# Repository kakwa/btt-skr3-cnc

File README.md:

# btt-skr3-cnc

Reviving a [Yeti Tool SmartBench](https://www.yetitool.com/) CNC router with new hardware and open-source firmware.

This project replaces pretty much all the sketchy eletronics original electronics with an even sketckier setup.

It keeps the original stepper motors, overal frame, and endstops.

## Project Status

* [done] Pi configuration
* [done] Base grblHAL setup
* [done] Wiring/adapter board
* [in-progress] End stops and safety stop configuration
* [in-progress] Proper enclosure for electronics
* [todo] Spindle control (optional)

## Hardware & Software components

| Component           | Details                                                          |
|---------------------|------------------------------------------------------------------|
| Controller board    | [BTT SKR 3 EZ](https://github.com/bigtreetech/SKR-3)             |
| Stepper drivers     | TMC5160                                                          |
| SBC                 | [BTT Pi](https://github.com/bigtreetech/BTT-Pi) (or RPi > 3)     |
| Firmware            | [grblHAL](https://github.com/grblHAL/core/blob/master/README.md) |
| UI & gCode Uploader | [gSender](https://sienci.com/gsender/)                           |
| Motors Setup        | X, Y, Z + ganged X2, Y2                                          |

## Repository Layout

- `docs/` — project documentation (start here); numbered markdown files covering intro, hardware, install, configuration, troubleshooting, and settings
- `ansible/` — Ansible playbook to provision the BTT Pi (roles: avahi, gsender, grblhal-builder, nginx, ...)
- `grblhal/` — grblHAL firmware as a git submodule (STM32 driver)
- `pcbs/` — KiCad PCB designs for the DB25 breakout boards and adapters
- `cad/` — FreeCAD enclosure and mounting parts
- `tests/` — G-code test files
- `misc/` — utility scripts and raw settings dumps

## Documentation

Project documentation is available in [`docs/`](docs/).

Salut c'est yann

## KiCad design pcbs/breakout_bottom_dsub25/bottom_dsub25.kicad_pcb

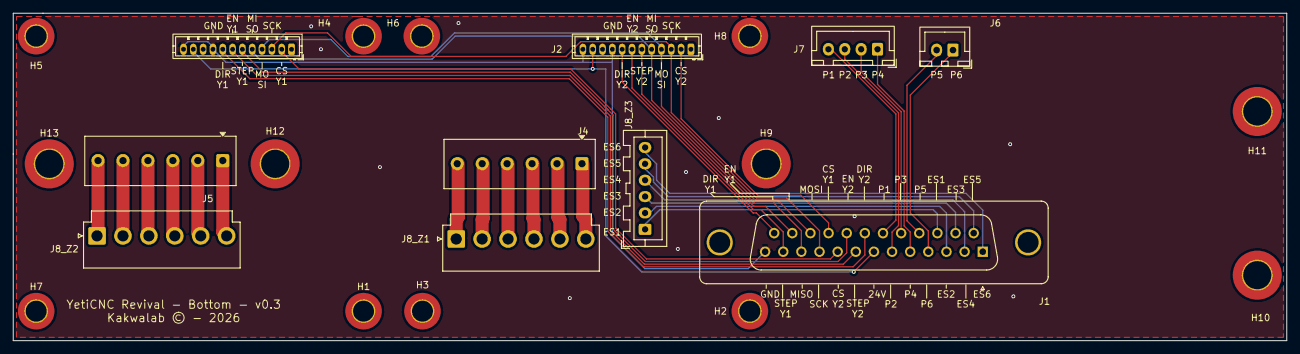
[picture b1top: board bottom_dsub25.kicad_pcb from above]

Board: 2 copper layers, 194.5 x 50.0 mm, 23 parts (0 on the bottom side), 37 nets.

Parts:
H1, H2, H3, H4, H5, H6, H7, H8: MountingHole; MountingHole_3.2mm_M3_DIN965_Pad_TopBottom
H9, H10, H11, H12, H13: MountingHole; MountingHole_4.3mm_M4_DIN965_Pad_TopBottom
J1: DB25_Pins; DSUB-25_Pins_Vertical_P2.77x2.84mm_MountingHoles
J2, J3: Conn_01x12; JST_ZH_B12B-ZR_1x12_P1.50mm_Vertical
J4, J5: Screw_Terminal_01x06; TerminalBlock_Phoenix_MKDS-1-6-3.81_1x06_P3.81mm_Horizontal
J6: Conn_01x02; JST_XH_B2B-XH-A_1x02_P2.50mm_Vertical
J7: Conn_01x04; JST_XH_B4B-XH-A_1x04_P2.50mm_Vertical
J8_Z1, J8_Z2: Conn_01x06_Pin; JST_VH_B6P-VH_1x06_P3.96mm_Vertical
J8_Z3: Conn_01x06_Pin; JST_XA_B06B-XASK-1_1x06_P2.50mm_Vertical

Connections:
GND: J1.13, J2.9, J2.12, J3.9, J3.12
unnamed: J1.14, J8_Z3.5
unnamed: J1.15, J8_Z3.3
unnamed: J1.16, J8_Z3.1
unnamed: J1.17, J6.2
unnamed: J1.18, J7.2
unnamed: J1.19, J7.4
unnamed: J1.20, J3.8
unnamed: J1.21, J3.6
unnamed: J1.22, J2.2
unnamed: J1.23, J2.4, J3.4
unnamed: J1.24, J2.6
unnamed: J1.25, J2.8
unnamed: J1.10, J2.3, J3.3
unnamed: J1.11, J2.5, J3.5
unnamed: J1.12, J2.7
unnamed: J1.7, J2.11, J3.11
unnamed: J1.9, J3.2
unnamed: J1.8, J3.7
unnamed: J4.1, J8_Z1.6
unnamed: J4.2, J8_Z1.5
unnamed: J4.3, J8_Z1.4
unnamed: J4.4, J8_Z1.3
unnamed: J4.5, J8_Z1.2
unnamed: J4.6, J8_Z1.1
unnamed: J5.1, J8_Z2.6
unnamed: J5.2, J8_Z2.5
unnamed: J5.3, J8_Z2.4
unnamed: J5.4, J8_Z2.3
unnamed: J5.5, J8_Z2.2
unnamed: J5.6, J8_Z2.1
unnamed: J1.4, J6.1
unnamed: J1.5, J7.1
unnamed: J1.6, J7.3
unnamed: J1.3, J8_Z3.2
unnamed: J1.2, J8_Z3.4
unnamed: J1.1, J8_Z3.6

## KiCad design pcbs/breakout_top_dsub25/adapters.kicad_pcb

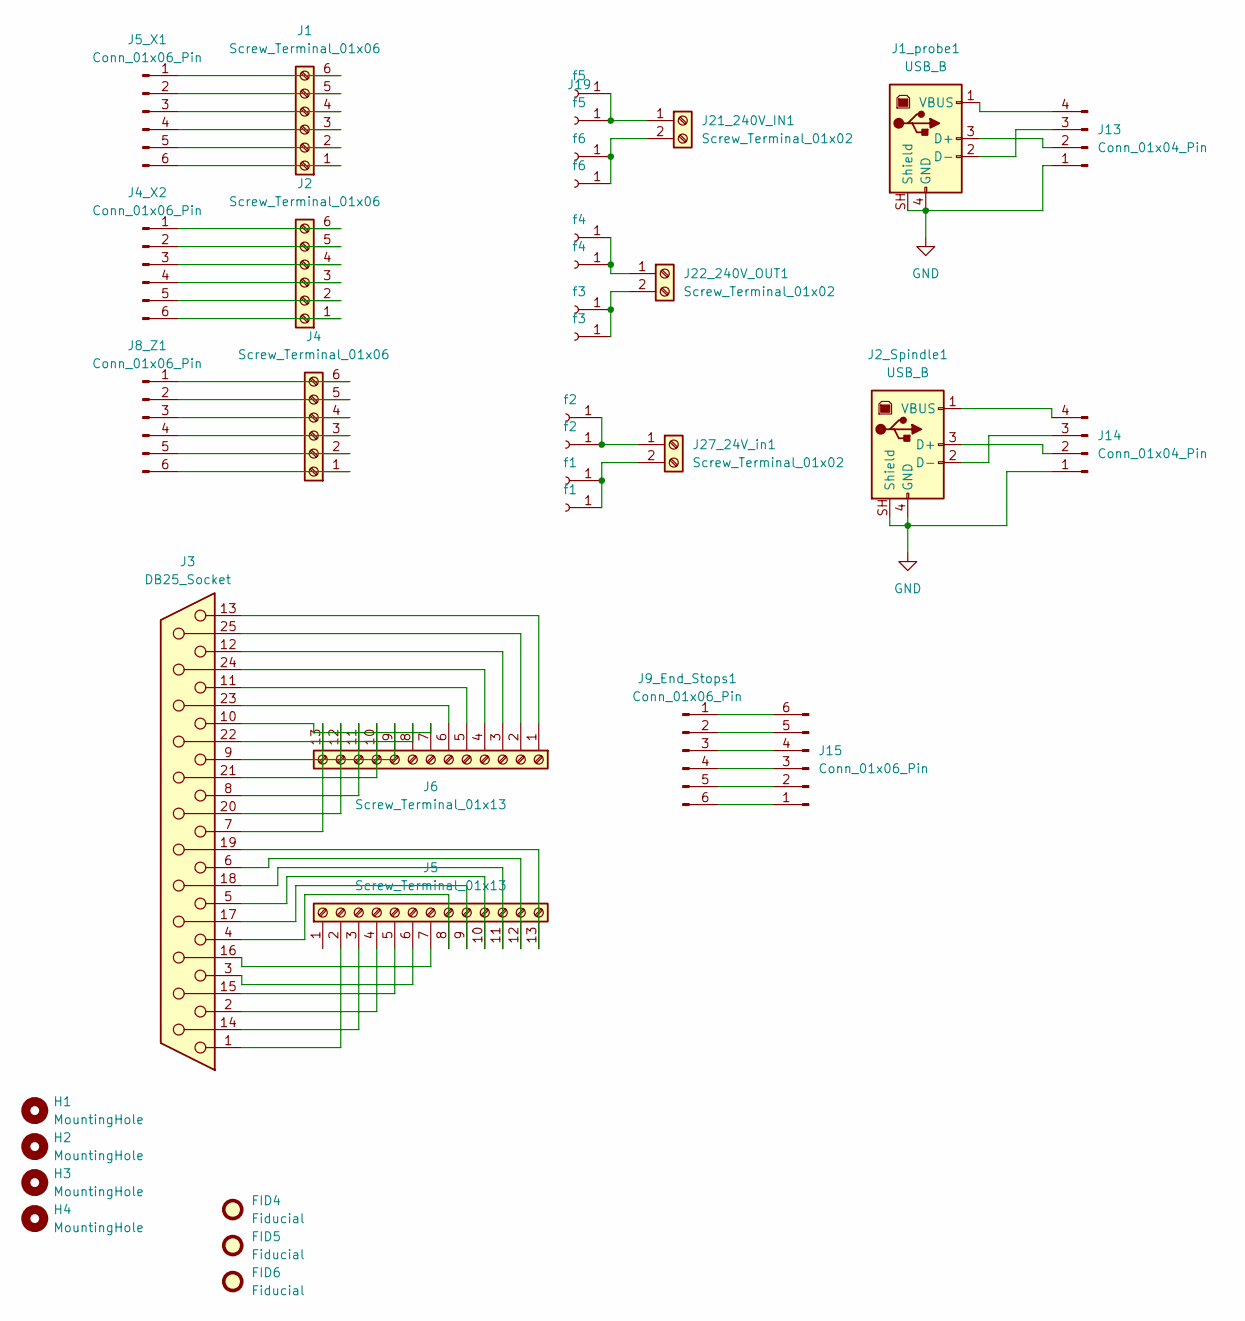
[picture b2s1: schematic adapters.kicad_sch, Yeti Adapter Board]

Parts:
F5: f5; SolderWire-1.5sqmm_1x01_D1.7mm_OD3mm
FID4, FID5, FID6: Fiducial; Fiducial_0.5mm_Mask2mm
H1, H2, H3, H4: MountingHole; MountingHole_3.2mm_M3_Pad_TopBottom
J1, J2, J4: Screw_Terminal_01x06; TerminalBlock_Phoenix_MKDS-1-6-3.81_1x06_P3.81mm_Horizontal
J1_probe1, J2_Spindle1: USB_B; USB_B_Lumberg_2411_02_Horizontal
J3: DB25_Socket; DSUB-25_Socket_Horizontal_P2.77x2.54mm_EdgePinOffset9.40mm
J4_X2, J5_X1: Conn_01x06_Pin; JST_VH_S6P-VH_1x06_P3.96mm_Horizontal
J5, J6: Screw_Terminal_01x13; TerminalBlock_Phoenix_MKDS-1-13-3.81_1x13_P3.81mm_Horizontal
J8_Z1, J9_End_Stops1: Conn_01x06_Pin; JST_XA_S06B-XASK-1N-BN_1x06_P2.50mm_Horizontal
J10, J11: f3; SolderWire-1.5sqmm_1x01_D1.7mm_OD3mm
J12, J16: f4; SolderWire-1.5sqmm_1x01_D1.7mm_OD3mm
J13, J14: Conn_01x04_Pin; JST_XH_B4B-XH-A_1x04_P2.50mm_Vertical
J15: Conn_01x06_Pin; JST_XH_B6B-XH-A_1x06_P2.50mm_Vertical
J17, J18: f6; SolderWire-1.5sqmm_1x01_D1.7mm_OD3mm
J19: f5; SolderWire-1.5sqmm_1x01_D1.7mm_OD3mm
J21_240V_IN1, J22_240V_OUT1, J27_24V_in1: Screw_Terminal_01x02; TerminalBlock_Phoenix_MKDS-1,5-2_1x02_P5.00mm_Horizontal
J23, J24: f2; SolderWire-1.5sqmm_1x01_D1.7mm_OD3mm
J25, J26: f1; SolderWire-1.5sqmm_1x01_D1.7mm_OD3mm

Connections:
GND: J1_probe1.4 (GND), J1_probe1.SH (Shield), J2_Spindle1.4 (GND), J2_Spindle1.SH (Shield), J13.1, J14.1
unnamed: F5.1 (Pin_1_1), J19.1 (Pin_1_1), J21_240V_IN1.1
unnamed: J1.1, J5_X1.6
unnamed: J1.2, J5_X1.5
unnamed: J1.3, J5_X1.4
unnamed: J1.4, J5_X1.3
unnamed: J1.5, J5_X1.2
unnamed: J1.6, J5_X1.1
unnamed: J2.1, J4_X2.6
unnamed: J2.2, J4_X2.5
unnamed: J2.3, J4_X2.4
unnamed: J2.4, J4_X2.3
unnamed: J2.5, J4_X2.2
unnamed: J2.6, J4_X2.1
unnamed: J3.14, J5.3
unnamed: J3.15, J5.5
unnamed: J3.16, J5.7
unnamed: J3.17, J5.9
unnamed: J3.18, J5.11
unnamed: J3.19, J5.13
unnamed: J3.20, J6.12
unnamed: J3.21, J6.10
unnamed: J3.22, J6.8
unnamed: J3.23, J6.6
unnamed: J3.24, J6.4
unnamed: J3.25, J6.2
unnamed: J4.1, J8_Z1.6
unnamed: J4.2, J8_Z1.5
unnamed: J4.3, J8_Z1.4
unnamed: J4.4, J8_Z1.3
unnamed: J4.5, J8_Z1.2
unnamed: J4.6, J8_Z1.1
unnamed: J3.1, J5.2
unnamed: J3.2, J5.4
unnamed: J3.3, J5.6
unnamed: J3.4, J5.8
unnamed: J3.5, J5.10
unnamed: J3.6, J5.12
unnamed: J3.13, J6.1
unnamed: J3.12, J6.3
unnamed: J3.11, J6.5
unnamed: J3.10, J6.7
unnamed: J3.9, J6.9
unnamed: J3.8, J6.11
unnamed: J3.7, J6.13
unnamed: J10.1 (Pin_1_1), J11.1 (Pin_1_1), J22_240V_OUT1.2
unnamed: J12.1 (Pin_1_1), J16.1 (Pin_1_1), J22_240V_OUT1.1
unnamed: J1_probe1.3 (D+), J13.2
unnamed: J1_probe1.2 (D-), J13.3
unnamed: J1_probe1.1 (VBUS), J13.4
unnamed: J2_Spindle1.3 (D+), J14.2
unnamed: J2_Spindle1.2 (D-), J14.3
unnamed: J2_Spindle1.1 (VBUS), J14.4
unnamed: J9_End_Stops1.6, J15.1
unnamed: J9_End_Stops1.5, J15.2
unnamed: J9_End_Stops1.4, J15.3
unnamed: J9_End_Stops1.3, J15.4
unnamed: J9_End_Stops1.2, J15.5
unnamed: J9_End_Stops1.1, J15.6
unnamed: J17.1 (Pin_1_1), J18.1 (Pin_1_1), J21_240V_IN1.2
unnamed: J23.1 (Pin_1_1), J24.1 (Pin_1_1), J27_24V_in1.1
unnamed: J25.1 (Pin_1_1), J26.1 (Pin_1_1), J27_24V_in1.2

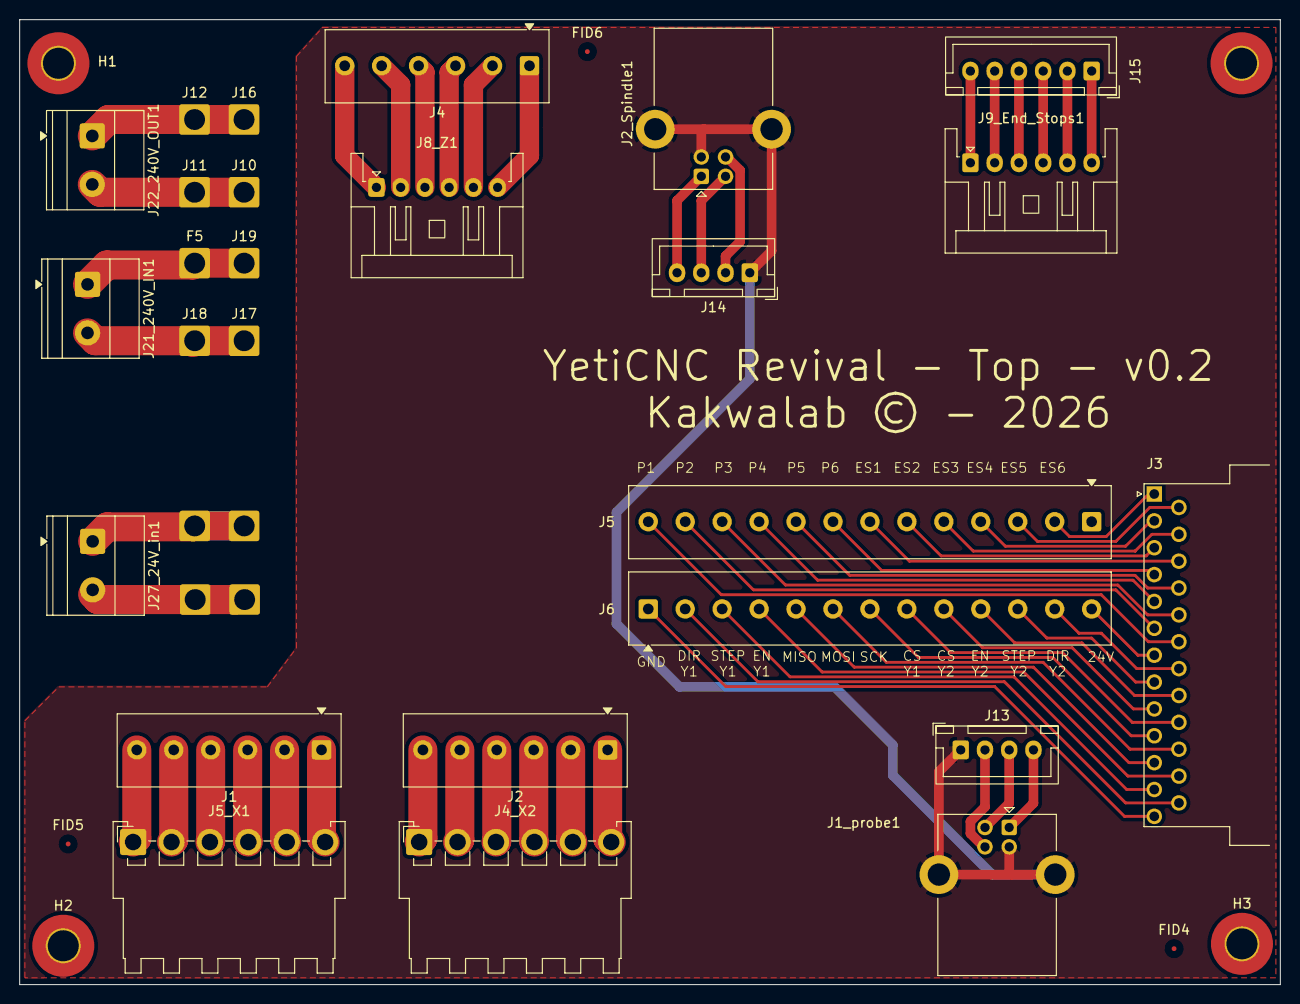
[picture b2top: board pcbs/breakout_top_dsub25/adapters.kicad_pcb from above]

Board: 2 copper layers, 130.0 x 99.5 mm, 37 parts (0 on the bottom side), 62 nets.

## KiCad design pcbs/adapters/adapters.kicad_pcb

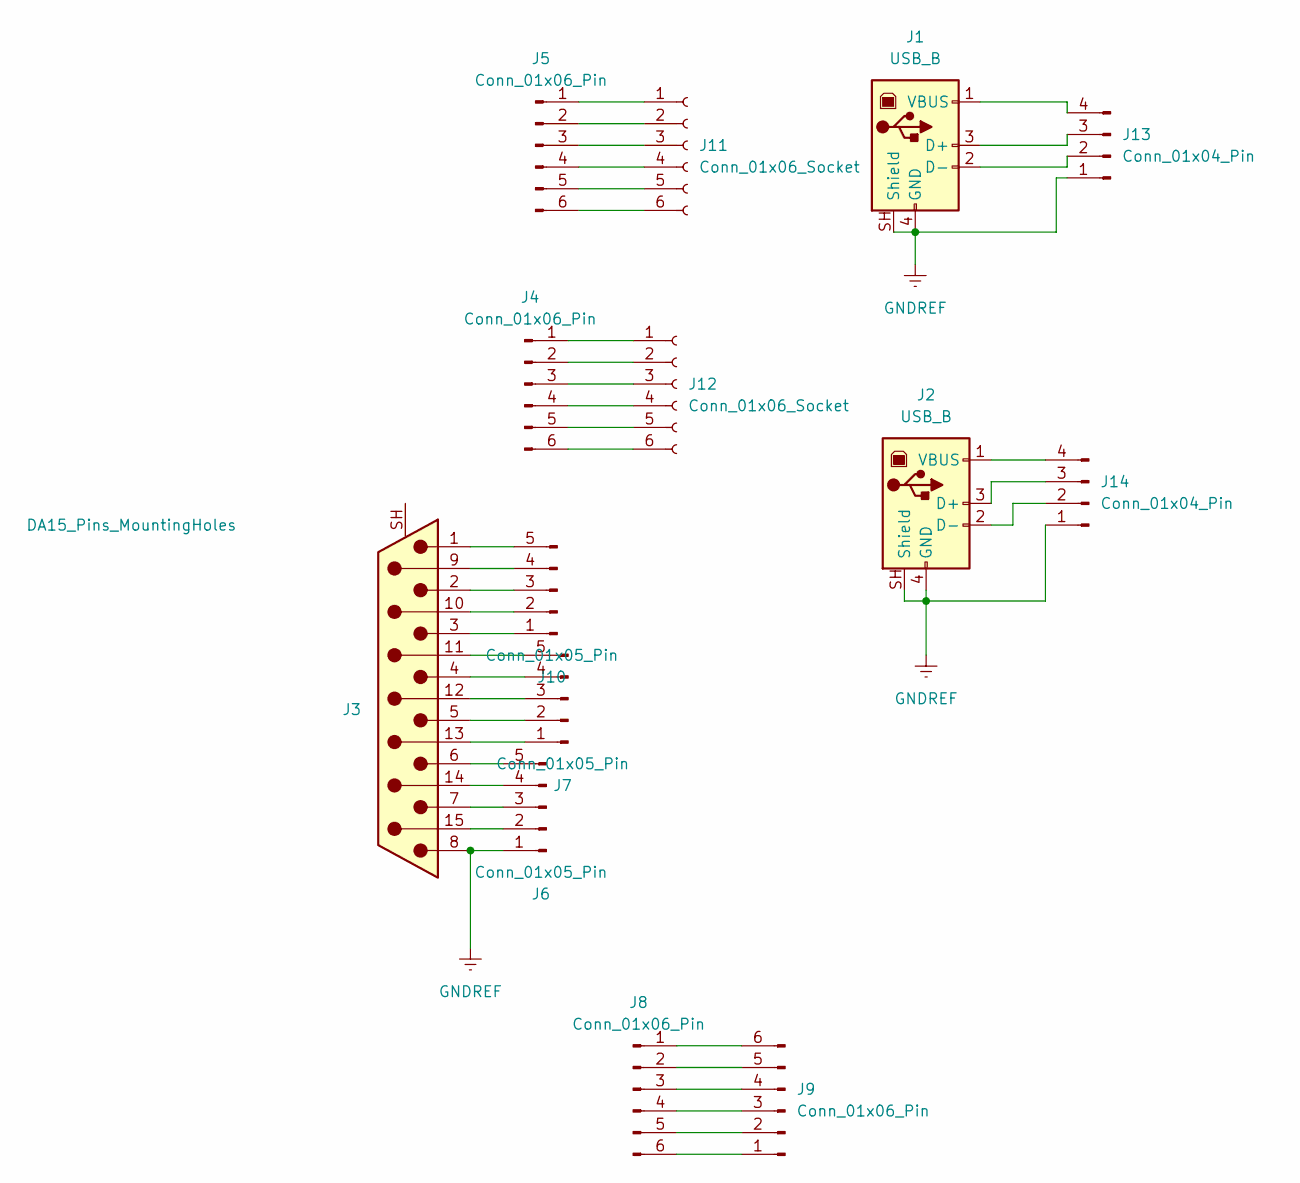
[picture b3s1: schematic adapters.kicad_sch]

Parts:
J1, J2: USB_B; USB_B_Lumberg_2411_02_Horizontal
J3: DA15_Pins_MountingHoles; DSUB-15-HD_Pins_Horizontal_P2.29x1.90mm_EdgePinOffset3.03mm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
J4, J5: Conn_01x06_Pin; JST_VH_S6P-VH_1x06_P3.96mm_Horizontal
J6, J7, J10: Conn_01x05_Pin; PinHeader_1x05_P2.54mm_Vertical
J8: Conn_01x06_Pin; JST_XA_S06B-XASK-1_1x06_P2.50mm_Horizontal
J9: Conn_01x06_Pin; PinHeader_1x06_P2.54mm_Vertical
J11, J12: Conn_01x06_Socket; PhoenixContact_MSTBA_2,5_6-G-5,08_1x06_P5.08mm_Horizontal
J13: Conn_01x04_Pin; PinHeader_1x04_P2.54mm_Vertical
J14: Conn_01x04_Pin

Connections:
GNDREF: J1.4 (GND), J1.SH (Shield), J2.4 (GND), J2.SH (Shield), J3.8, J6.1, J13.1, J14.1
unnamed: J1.3 (D+), J13.3
unnamed: J1.2 (D-), J13.2
unnamed: J1.1 (VBUS), J13.4
unnamed: J3.12, J7.3
unnamed: J3.13, J7.1
unnamed: J3.14, J6.4
unnamed: J3.15, J6.2
unnamed: J3.11 (P111), J7.5
unnamed: J3.7, J6.3
unnamed: J3.6, J6.5
unnamed: J3.5, J7.2
unnamed: J3.4, J7.4
unnamed: J8.1, J9.6
unnamed: J8.2, J9.5
unnamed: J8.3, J9.4
unnamed: J8.4, J9.3
unnamed: J8.5, J9.2
unnamed: J8.6, J9.1
unnamed: J3.3, J10.1
unnamed: J3.10, J10.2
unnamed: J3.2, J10.3
unnamed: J3.9, J10.4
unnamed: J3.1, J10.5
unnamed: J5.1, J11.1
unnamed: J5.2, J11.2
unnamed: J5.3, J11.3
unnamed: J5.4, J11.4
unnamed: J5.5, J11.5
unnamed: J5.6, J11.6
unnamed: J4.1, J12.1
unnamed: J4.2, J12.2
unnamed: J4.3, J12.3
unnamed: J4.4, J12.4
unnamed: J4.5, J12.5
unnamed: J4.6, J12.6
unnamed: J2.2 (D-), J14.2
unnamed: J2.3 (D+), J14.3
unnamed: J2.1 (VBUS), J14.4

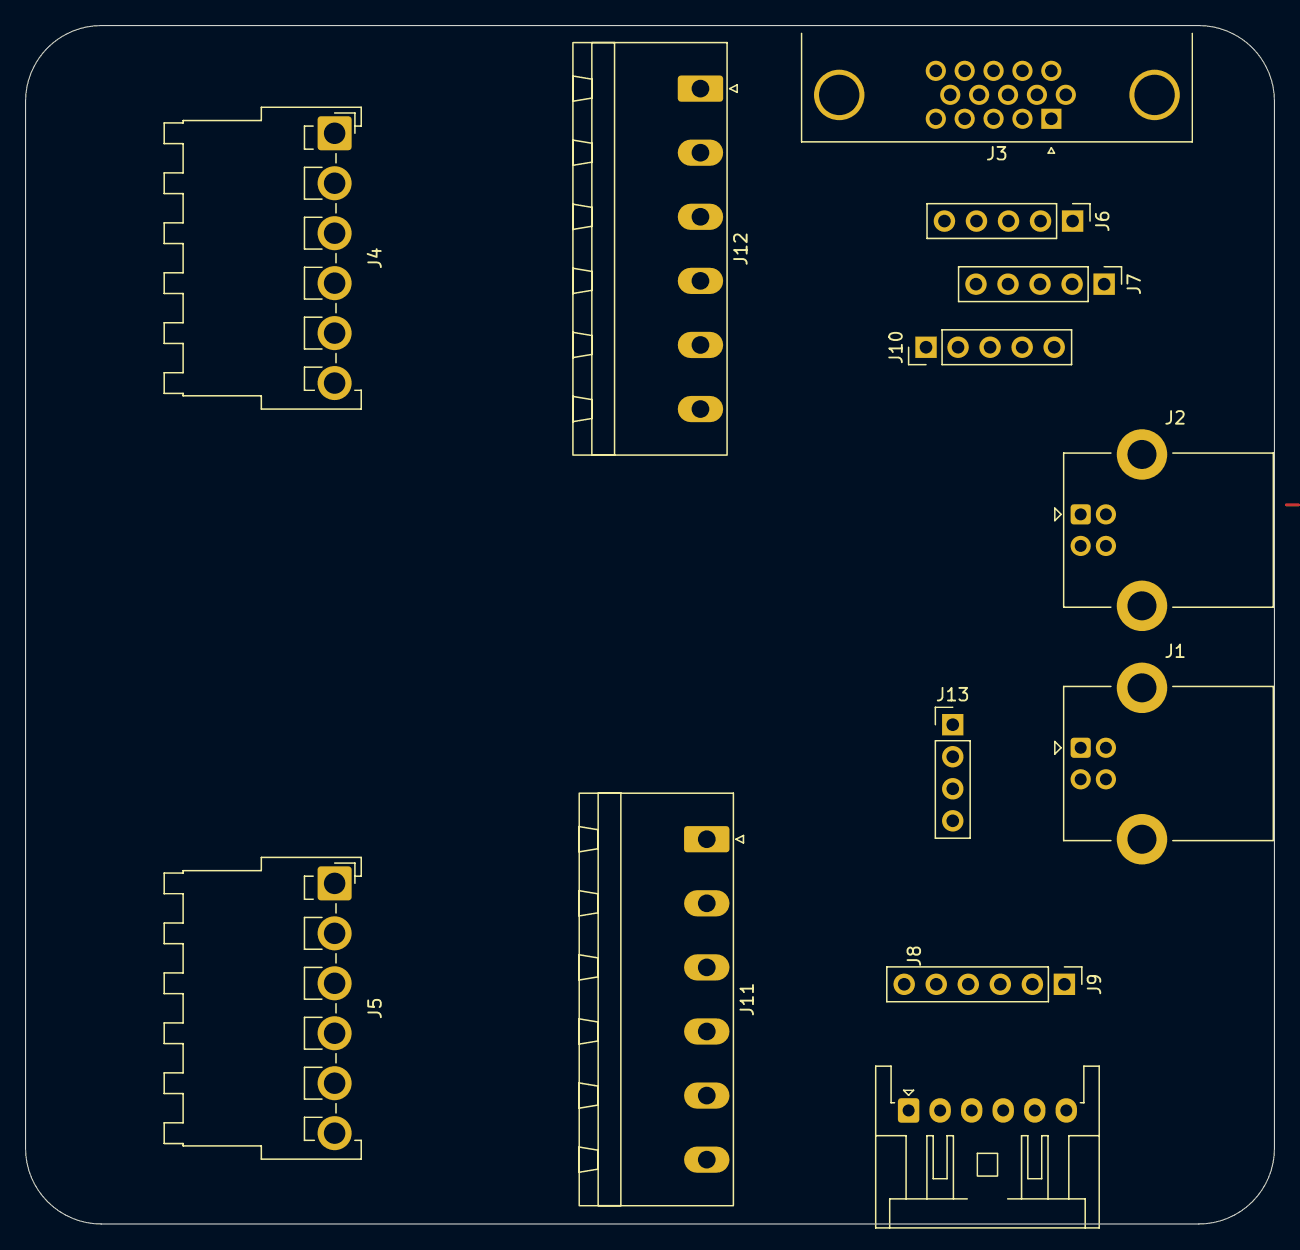
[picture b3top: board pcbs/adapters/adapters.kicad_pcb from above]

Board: 2 copper layers, 99.0 x 95.0 mm, 13 parts (0 on the bottom side), 36 nets.

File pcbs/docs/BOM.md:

# Bill of Materials

Every part: refdes, MPN, value, package, and WHY it was chosen. MPNs the agent
introduces without a datasheet check are flagged UNVERIFIED.

Value holds the component value only ("4.7uF", "1M", "500mAh Li-Po") — the
schematic stage draws it as the symbol's Value field, so a description there
collides with neighbouring symbols and fails the legibility gate. Prose belongs
in Rationale. One row per refdes; a grouped row ("C5-C8") matches no symbol.

| Refdes | Value | Footprint | MPN | Rationale |
|---|---|---|---|---|
| FID1 | Fiducial |  | UNVERIFIED | extracted from schematic by copperhead init |
| FID2 | Fiducial |  | UNVERIFIED | extracted from schematic by copperhead init |
| FID3 | Fiducial |  | UNVERIFIED | extracted from schematic by copperhead init |
| H1 | MountingHole | MountingHole:MountingHole_3.2mm_M3_DIN965_Pad_TopBottom | UNVERIFIED | extracted from schematic by copperhead init |
| H2 | MountingHole | MountingHole:MountingHole_3.2mm_M3_DIN965_Pad_TopBottom | UNVERIFIED | extracted from schematic by copperhead init |
| H3 | MountingHole | MountingHole:MountingHole_3.2mm_M3_DIN965_Pad_TopBottom | UNVERIFIED | extracted from schematic by copperhead init |
| H4 | MountingHole | MountingHole:MountingHole_3.2mm_M3_DIN965_Pad_TopBottom | UNVERIFIED | extracted from schematic by copperhead init |
| H5 | MountingHole | MountingHole:MountingHole_3.2mm_M3_DIN965_Pad_TopBottom | UNVERIFIED | extracted from schematic by copperhead init |
| H6 | MountingHole | MountingHole:MountingHole_3.2mm_M3_DIN965_Pad_TopBottom | UNVERIFIED | extracted from schematic by copperhead init |
| H7 | MountingHole | MountingHole:MountingHole_3.2mm_M3_DIN965_Pad_TopBottom | UNVERIFIED | extracted from schematic by copperhead init |
| H8 | MountingHole | MountingHole:MountingHole_3.2mm_M3_DIN965_Pad_TopBottom | UNVERIFIED | extracted from schematic by copperhead init |
| H9 | MountingHole | MountingHole:MountingHole_4.3mm_M4_DIN965_Pad_TopBottom | UNVERIFIED | extracted from schematic by copperhead init |
| H10 | MountingHole | MountingHole:MountingHole_4.3mm_M4_DIN965_Pad_TopBottom | UNVERIFIED | extracted from schematic by copperhead init |
| H11 | MountingHole | MountingHole:MountingHole_4.3mm_M4_DIN965_Pad_TopBottom | UNVERIFIED | extracted from schematic by copperhead init |
| H12 | MountingHole | MountingHole:MountingHole_4.3mm_M4_DIN965_Pad_TopBottom | UNVERIFIED | extracted from schematic by copperhead init |
| H13 | MountingHole | MountingHole:MountingHole_4.3mm_M4_DIN965_Pad_TopBottom | UNVERIFIED | extracted from schematic by copperhead init |
| J1 | DB25_Pins | Connector_Dsub:DSUB-25_Pins_Vertical_P2.77x2.84mm_MountingHoles | UNVERIFIED | extracted from schematic by copperhead init |
| J2 | Conn_01x12 | Connector_JST:JST_ZH_B12B-ZR_1x12_P1.50mm_Vertical | UNVERIFIED | extracted from schematic by copperhead init |
| J3 | Conn_01x12 | Connector_JST:JST_ZH_B12B-ZR_1x12_P1.50mm_Vertical | UNVERIFIED | extracted from schematic by copperhead init |
| J4 | Screw_Terminal_01x06 | TerminalBlock_Phoenix:TerminalBlock_Phoenix_MKDS-1-6-3.81_1x06_P3.81mm_Horizontal | UNVERIFIED | extracted from schematic by copperhead init |
| J5 | Screw_Terminal_01x06 | TerminalBlock_Phoenix:TerminalBlock_Phoenix_MKDS-1-6-3.81_1x06_P3.81mm_Horizontal | UNVERIFIED | extracted from schematic by copperhead init |
| J6 | Conn_01x02 | Connector_JST:JST_XH_B2B-XH-A_1x02_P2.50mm_Vertical | UNVERIFIED | extracted from schematic by copperhead init |
| J7 | Conn_01x04 | Connector_JST:JST_XH_B4B-XH-A_1x04_P2.50mm_Vertical | UNVERIFIED | extracted from schematic by copperhead init |
| J8_Z1 | Conn_01x06_Pin | Connector_JST:JST_VH_B6P-VH_1x06_P3.96mm_Vertical | UNVERIFIED | extracted from schematic by copperhead init |
| J8_Z2 | Conn_01x06_Pin | Connector_JST:JST_VH_B6P-VH_1x06_P3.96mm_Vertical | UNVERIFIED | extracted from schematic by copperhead init |
| J8_Z3 | Conn_01x06_Pin | Connector_JST:JST_XA_B06B-XASK-1_1x06_P2.50mm_Vertical | UNVERIFIED | extracted from schematic by copperhead init |

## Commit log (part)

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2026-01-16 base setup for ansible
2026-01-16 submodule
2026-01-16 remove repo
2026-01-16 clean-up
2026-01-16 add submodule for real this time
2026-01-16 skeleton for the gsender module
2026-01-16 update ansible submodule
2026-01-16 adding missing handler
2026-01-16 adding gsender service
2026-01-17 fix binary path for gsender
2026-01-17 adding the remote/headless flag
2026-01-17 use xvfb (gsender requires an X11 server)
2026-01-17 use wayland xwfb-run instead + gsender in video group
    a bit more futur process, and less complaints about acceleration (might
    also be because of group video
2026-01-17 switch to xwayland-run
2026-01-17 rsyslog tweaks
2026-01-19 notes
2026-01-22 adding notes
2026-01-23 grblhal submodule for STM32H7
2026-01-23 split nginx and gsenser role
2026-01-23 adding role to setup build tools for grblhal
2026-01-23 fixed ports for avahi
2026-01-24 workaround for build
2026-01-24 header + notes
2026-01-28 update grblhal
2026-01-28 adding rough version of my_machince.h
2026-01-28 deploy our configuration header
2026-01-28 adding symlink for convinience
2026-01-28 tweak build and flash + NOTES
2026-01-28 more complete documentation
2026-01-31 put the ganged #defined in the platform.io file (otherwise they don't seem to be takken into accont)
2026-01-31 switch to everything defined in my_machine.h
2026-02-19 update submodule
2026-03-17 remove personal roles
2026-03-17 adding instruction for the setup
2026-03-17 add basic setup instruction
2026-03-17 Fix repos role: install python3-debian dependency
    Made-with: Cursor
2026-03-17 Fix nginx role: use ansible_facts instead of deprecated ansible_hostname
    Made-with: Cursor
2026-03-17 re-enable repo setup
2026-03-17 Fix grblhal-builder role: use ansible_facts instead of deprecated ansible_architecture
    Made-with: Cursor
2026-03-17 Fix grblhal-builder defaults: use ansible_facts instead of deprecated ansible_user_id
    Made-with: Cursor
2026-03-17 Fix grblhal-builder: set build user/group to root explicitly
    Made-with: Cursor
2026-03-17 Fix grblhal-builder: allow platformio.ini to be copied so it can be patched
    Made-with: Cursor
2026-03-18 adding xauth
2026-03-18 adding an ignore errors for platformio init
2026-03-18 set limits and build number
2026-03-18 trigger apt cache update when appropriate
2026-03-18 complete the ansible stuff
2026-03-18 adding flashing instruction
2026-03-18 skeleton for the wiring
2026-03-18 basic pinout configuration
2026-03-18 enable the Safety Door ping (to be used for the collision bars)
2026-03-20 Add board labels and remove MAX switchs limits
2026-03-20 clean-up README
2026-03-21 adding documentation for pins
2026-03-21 tweaks
2026-03-21 customize btt_skr_v3.0_map.h directly
2026-04-11 adding todo list
2026-04-14 adding skeleton for pcb
2026-04-16 remove adapter
2026-04-29 PCB draft tweaks + ignores
2026-04-30 first rough version of top board
2026-05-01 rename
2026-05-01 adding a dsub 25 variant + tweaks
2026-05-03 adding project for bottom page
2026-05-07 progress on the bottom board (most connectors, etc)
2026-05-09 rough component positioning for bottom pcb + add connectors
2026-05-09 add routinng
2026-05-10 adding various silk layer labels
2026-05-10 tweak top board
    add mounting holes in the middle (enable zip for cables?)
    reposition a few components
    fix some rules warnings
2026-05-10 adding ground plan
2026-05-10 add version/name
2026-05-10 adding Makefile to generate the gerbel files
2026-05-10 don't commit zip files (gerbel)
2026-05-26 adding trying to set some inversion mask
2026-05-26 version bump
2026-05-28 Add DHCP server setup instructions for ethernet connectivity
2026-05-29 quick router setup script
2026-05-29 better README
2026-05-29 adding SDCARD definition
2026-06-04 adding stands cad model
2026-06-04 increase size of standoff
2026-06-10 4mm diameter for the stand legs of the driver mounts
2026-06-10 adding backplate for bottom PCB
2026-06-10 adding refresh page for nginx
2026-06-10 configuration clean-up
2026-06-13 trying to clean-up build
2026-06-13 lower current
2026-06-13 rollback grbhal
2026-06-15 more conservative values
2026-06-15 add cnc console helper + set grbhal to latest version
2026-06-15 update version
2026-06-15 creating a dedicated plateform.io section for our machine
2026-06-16 adding verbose flag
2026-06-16 switch to the correct board
2026-06-16 fix board CPU
2026-06-16 don't for the SPI_ENABLE define
2026-06-16 more options to try to force SPI
2026-06-16 set build info
2026-06-16 adding raw settings.txt $HELP
2026-06-16 adding settings documentation
2026-06-16 clean-up troubleshooting
2026-06-16 complete intro
2026-06-16 reorganize and clean-up the documenation
2026-06-16 various clean-up
2026-06-16 clean-up AI slop
2026-06-16 change the order
2026-06-16 adding README symlink
2026-06-16 fix typo
2026-06-16 another gotcha
2026-06-16 adding todo of what is needed for this doc
2026-06-16 move and clean-up main readme instructions into notes
2026-06-16 README
2026-06-16 improvements
2026-06-17 Revise limit switch port mapping in 01_HARDWARE.md
    Updated limit switch port mapping table in hardware documentation.
2026-06-17 wire-in the 24V from the main board + wire ground on this pin
2026-06-17 adding bottom backplate
2026-06-17 relabel dsub 25 pins which were rewired/renumbered for 24V routing + add spacing for power supply stuff.
2026-06-17 remove the vga project
2026-06-17 adding a TODO
2026-06-17 rework the intro
2026-06-17 rough hardware draft
2026-06-18 adding photos
2026-06-18 fix typos
2026-06-19 bottom PCBs, correct hole placement + grounded plane + remove warnings
2026-06-19 reorg of cad stuff + add drag chain links
2026-06-19 adding drag chain
2026-06-19 adding the ends for the drag chains
2026-06-20 rought draft of the wiring schemas
2026-06-20 rework sections a bit
2026-06-20 adding warning for stepper mirrored
2026-06-20 clarify doc
2026-06-20 tweaks for the configuration and calibration
2026-06-22 adding some comments
2026-06-22 clean-up options
2026-06-22 switch to 4 spaces indent + tweak shape
    tweaks:
    * 45 angles
    * rounded base
    * tighter tolerances
2026-06-22 adding flags for the legs
2026-06-22 add support for legs
2026-06-22 switch back to not rounding stuff (otherwise, chain flex too much on the other side)
2026-06-22 remove now useless freecad end chain
2026-06-22 better names for the stl files
2026-06-22 adding tolerances for the clip
2026-06-22 add makefiles and clean-up stls
2026-06-25 update values for steps per mm with more real world stuff
2026-06-25 merge
